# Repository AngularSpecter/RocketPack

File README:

*** Rocket Pack************************************

Project Synopsis
--------------------

Rocket pack is a development board based around the MSP430FR5739 microcontroller
and the Digi Xbee S3B Pro 900MHz zigbee radio.  The board is intended to 
facilitate broadcasting real time, high-rate sensor data over a range of several
hundred meters.  The board is designed to interface with custom built sensor 
packages, or with the TI sensorTag development board running custom firmware

Power Supply
----------------------
The board has on-board battery management designed specifically for single cell
lipo batteries, but will also take any voltage source between 3.3V and 5VDC.
The regualted 3.2V rail is availible on all three expansion headers as well as 
the CCdebugger header, which is designed specifically to power the sensorTag
development board.   

Communications
----------------------
The MSP430FR5739 contains two hardware USART's.  One USART is reserved for the
zigbee radio, while the other is broken out to both the serial data header and 
the ez430 programming/debug header.  All signals reqired for I2C, SPI or UART 
are availible on the serial data header

The firmware is written to buffer both inbound and outbound traffic.  The MCU 
pops bytes into the rx buffers in low power mode.  Once a line term char is RX'd,
LPM is exited and the full packet is processed.

No data is transmitted until a full packet is buffered.  Then it is transmitted
entirely before additional data is processed.  

Node power up sequence
-----------------------------------

sleep loop
-----------
1. Boot
2. Hold sensors in reset
3. Read and store radio address
4. Boot sensors
5. Read and store cal data
6. Sleep sensors

{
Auto discovery
---------------------
1. Poll magentometer
2. Broadcast host discover on trigger
3. Repeat until node select rxd
4. TX ACK
}

Wake up loop (on rx of node select)
-------------
7. TX ACK
8. Wait for command
   8a. Send cal data
   8b. Start data stream
  
On ~node select
----------------
1. Sleep sensors
2. Wait for wake up 

  Packet Formatting
  -----------------------------------------
  [0x01] [address] [0x00]
  host discover   0x01     Broadcast by the host to the base station to announce
                           its presence.
  [0x02] [command] [data] [0x00]                         
  command         0x02     Base -> node: command for remote node to execute
                           node -> base: return of command
                           
                  commands
                     0x01  Stop transmitting data
                     0x02  Start transmitting data
                     0x03  Change sensor profile
                     0x04  Reboot         

  cal data        0x03     Base -> node: Request calibration data 
                           node -> base: Return calibration data   
  
  data packet     0x04     node -> base: Data 

  node select     0x05     base -> node: address of node to be active..all other sleep

  ACK             0x06     command ACK
  
  NACK            0x07     command NACK
SensorTag
----------------------

 Errata
 ---------------------
 
 V0.1:
       Debug header location:  The location of the debug header interferes with 
       nearby pin headers, making it impossible to populate the debug header 
       with a right angle header and .1" pitch pin header.
       
       Specified load capacitors on the crystal are wrong.  The crystal will 
       stabilize on boot, but will not remain.
       
       Radio CONFIG pin is wired to MCU to allow easy entrance into command
       mode.  This should be connected to a different pin.

TO DO
------------------------

1.  MS430Firmware:  1.  Startup sleep mode -> poll mag and exit on high value
                    2.  Startup procedure -> broadcast calibration data
                    3.  Startup procedure -> read radio ID to store UID
                    4.  TX mirror         -> Prepend UID to TX'd packets
                    
2.  SensorTag       1.  Clean up firmware  -> remove deadwood
                    2.  
                    
3.  Labview         1.  Radio interface  ->  AT command mode control to select
                                             radio to listen to
                    2.  Sensor interface ->  Formalize calibration code
                    3.  Sensor interface ->  Formalize data processing
                    4.  Sensor interface ->  Add "remote globals"

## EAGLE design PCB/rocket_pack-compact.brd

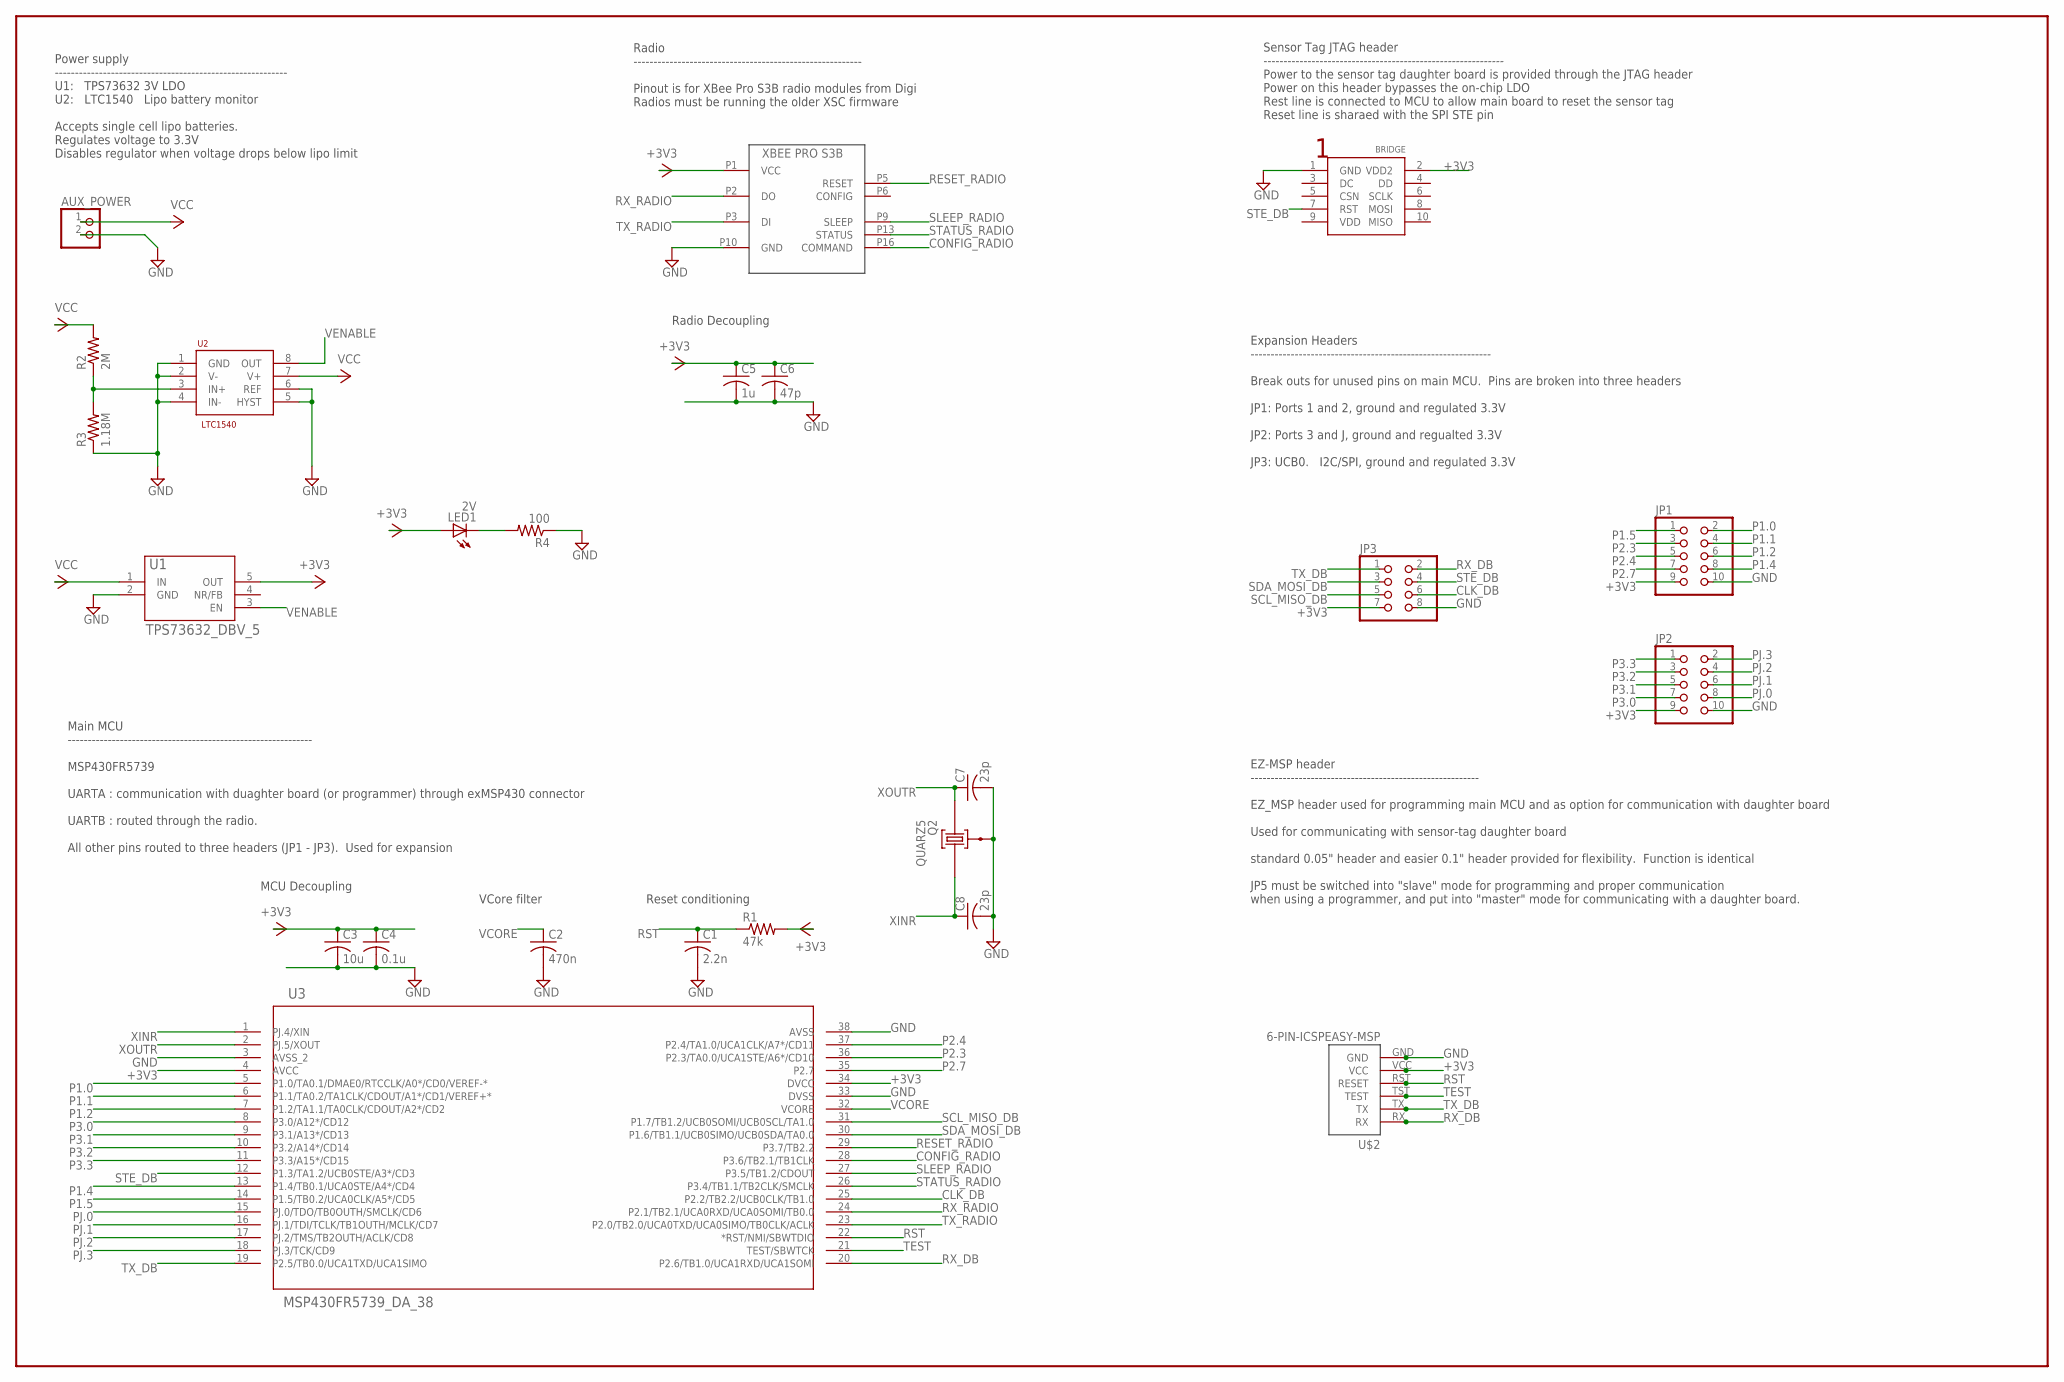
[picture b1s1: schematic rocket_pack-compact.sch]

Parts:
AUX_POWER: PINHD-1X2; 1X02
BRIDGE: CC-DEBUG; 2X5-1.27MM
C1: 2.2n; C1206
C2: 470n; C1206
C3: 10u; C1206
C4: 0.1u; C1206
C5: 1u; C1206
C6: 47p; C1206
C7, C8: 23p; C1206
JP1, JP2: PINHD-2X5; 2X05
JP3: PINHD-2X4; 2X04
LED1: 2V; 1206
Q2: QUARZ5
R1: 47k; R1206
R2: 2M; R1206
R3: 1.18M; R1206
R4: 100; R1206
U1: TPS73632_DBV_5; DBV5
U2: LTC1540; S8
U3: MSP430FR5739_DA_38; DA38
U$1: XBEE_PRO_S3B; PRO_S3B
U$2: 6-PIN-ICSPEASY-MSP; EASYMSP-6PIN

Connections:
+3V3: BRIDGE.2 (VDD2), C3.1, C4.1, C5.1, C6.1, JP1.9, JP2.9, JP3.7, LED1.A, R1.2, U1.5 (OUT), U3.4 (AVCC), U3.34 (DVCC), U$1.P1 (VCC), U$2.VCC
CLK_DB: JP3.6, U3.25 (P2.2/TB2.2/UCB0CLK/TB1.0)
CONFIG_RADIO: U3.28 (P3.6/TB2.1/TB1CLK), U$1.P16 (COMMAND)
GND: AUX_POWER.2, BRIDGE.1 (GND), C1.2, C2.2, C3.2, C4.2, C5.2, C6.2, C7.2, C8.2, JP1.10, JP2.10, JP3.8, Q2.GND@0 (0), R3.1, R4.1, U1.2 (GND), U2.1 (GND), U2.2 (V-), U2.4 (IN-), U2.5 (HYST), U2.6 (REF), U3.3 (AVSS_2), U3.33 (DVSS), U3.38 (AVSS), U$1.P10 (GND), U$2.GND
LED: LED1.C, R4.2
unnamed: R2.1, R3.2, U2.3 (IN+)
P1.0: JP1.2, U3.5 (P1.0/TA0.1/DMAE0/RTCCLK/A0*/CD0/VEREF-*)
P1.1: JP1.4, U3.6 (P1.1/TA0.2/TA1CLK/CDOUT/A1*/CD1/VEREF+*)
P1.2: JP1.6, U3.7 (P1.2/TA1.1/TA0CLK/CDOUT/A2*/CD2)
P1.4: JP1.8, U3.13 (P1.4/TB0.1/UCA0STE/A4*/CD4)
P1.5: JP1.1, U3.14 (P1.5/TB0.2/UCA0CLK/A5*/CD5)
P2.3: JP1.3, U3.36 (P2.3/TA0.0/UCA1STE/A6*/CD10)
P2.4: JP1.5, U3.37 (P2.4/TA1.0/UCA1CLK/A7*/CD11)
P2.7: JP1.7, U3.35 (P2.7)
P3.0: JP2.7, U3.8 (P3.0/A12*/CD12)
P3.1: JP2.5, U3.9 (P3.1/A13*/CD13)
P3.2: JP2.3, U3.10 (P3.2/A14*/CD14)
P3.3: JP2.1, U3.11 (P3.3/A15*/CD15)
PJ.0: JP2.8, U3.15 (PJ.0/TDO/TB0OUTH/SMCLK/CD6)
PJ.1: JP2.6, U3.16 (PJ.1/TDI/TCLK/TB1OUTH/MCLK/CD7)
PJ.2: JP2.4, U3.17 (PJ.2/TMS/TB2OUTH/ACLK/CD8)
PJ.3: JP2.2, U3.18 (PJ.3/TCK/CD9)
RESET_RADIO: U3.29 (P3.7/TB2.2), U$1.P5 (RESET)
RST: C1.1, R1.1, U3.22 (*RST/NMI/SBWTDIO), U$2.RST (RESET)
RX_DB: JP3.2, U3.20 (P2.6/TB1.0/UCA1RXD/UCA1SOMI), U$2.RX
RX_RADIO: U3.24 (P2.1/TB2.1/UCA0RXD/UCA0SOMI/TB0.0), U$1.P2 (DO)
SCL_MISO_DB: JP3.5, U3.31 (P1.7/TB1.2/UCB0SOMI/UCB0SCL/TA1.0)
SDA_MOSI_DB: JP3.3, U3.30 (P1.6/TB1.1/UCB0SIMO/UCB0SDA/TA0.0)
SLEEP_RADIO: U3.27 (P3.5/TB1.2/CDOUT), U$1.P9 (SLEEP)
STATUS_RADIO: U3.26 (P3.4/TB1.1/TB2CLK/SMCLK), U$1.P13 (STATUS)
STE_DB: BRIDGE.7 (RST), JP3.4, U3.12 (P1.3/TA1.2/UCB0STE/A3*/CD3)
TEST: U3.21 (TEST/SBWTCK), U$2.TST (TEST)
TX_DB: JP3.1, U3.19 (P2.5/TB0.0/UCA1TXD/UCA1SIMO), U$2.TX
TX_RADIO: U3.23 (P2.0/TB2.0/UCA0TXD/UCA0SIMO/TB0CLK/ACLK), U$1.P3 (DI)
VCC: AUX_POWER.1, R2.2, U1.1 (IN), U2.7 (V+)
VCORE: C2.1, U3.32 (VCORE)
VENABLE: U1.3 (EN), U2.8 (OUT)
XINR: C8.1, Q2.1, U3.1 (PJ.4/XIN)
XOUTR: C7.1, Q2.2, U3.2 (PJ.5/XOUT)

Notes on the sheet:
Radio Decoupling
MCU Decoupling
Power supply ---------------------------------------------------------- U1: TPS73632 3V LDO U2: LTC1540 Lipo battery monitor Accepts single cell lipo batteries. Regulates voltage to 3.3V Disables regulator when voltage drops below lipo limit
Radio --------------------------------------------------------- Pinout is for XBee Pro S3B radio modules from Digi Radios must be running the older XSC firmware
Sensor Tag JTAG header ------------------------------------------------------------ Power to the sensor tag daughter board is provided through the JTAG header Power on this header bypasses the on-chip LDO Rest line is connected to MCU to allow main board to reset the sensor tag Reset line is sharae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
Reset conditioning
VCore filter
Main MCU ------------------------------------------------------------- MSP430FR5739 UARTA : communication with duaghter board (or programmer) through exMSP430 connector UARTB : routed through the radio. All other pins routed to three headers (JP1 - JP3). Used for expansion
EZ-MSP header --------------------------------------------------------- EZ_MSP header used for programming main MCU and as option for communication with daughter board Used for communicating with sensor-tag daughter board standard 0.05" header and easier 0.1" header provided for flexibility. Functi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
Expansion Headers ------------------------------------------------------------ Break outs for unused pins on main MCU. Pins are broken into three headers JP1: Ports 1 and 2, ground and regulated 3.3V JP2: Ports 3 and J, ground and regualted 3.3V JP3: UCB0. I2C/SPI, ground and regulated 3.3V

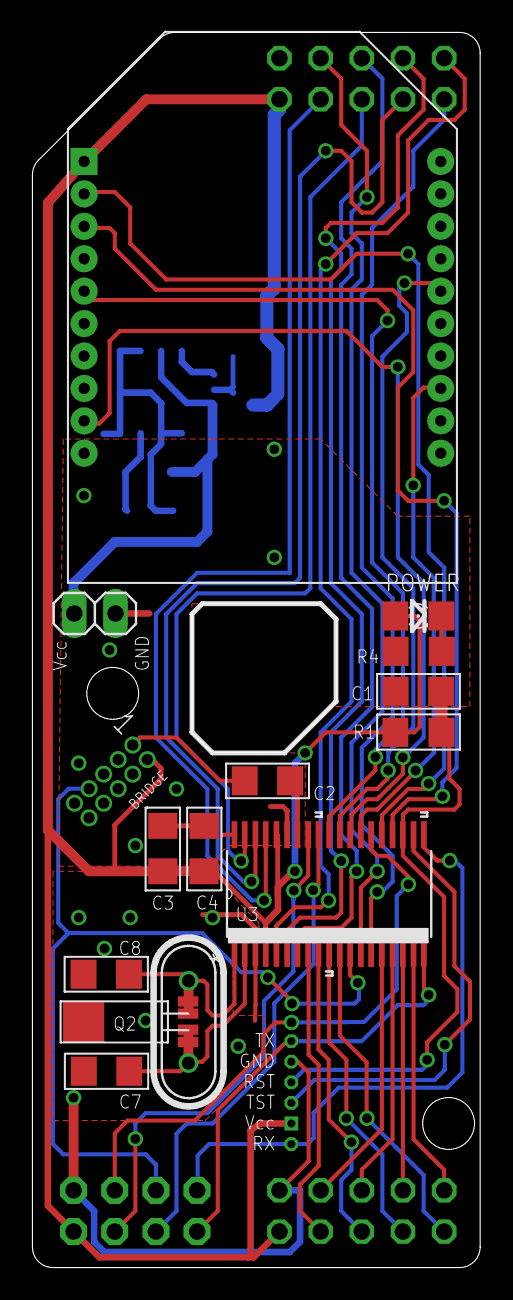
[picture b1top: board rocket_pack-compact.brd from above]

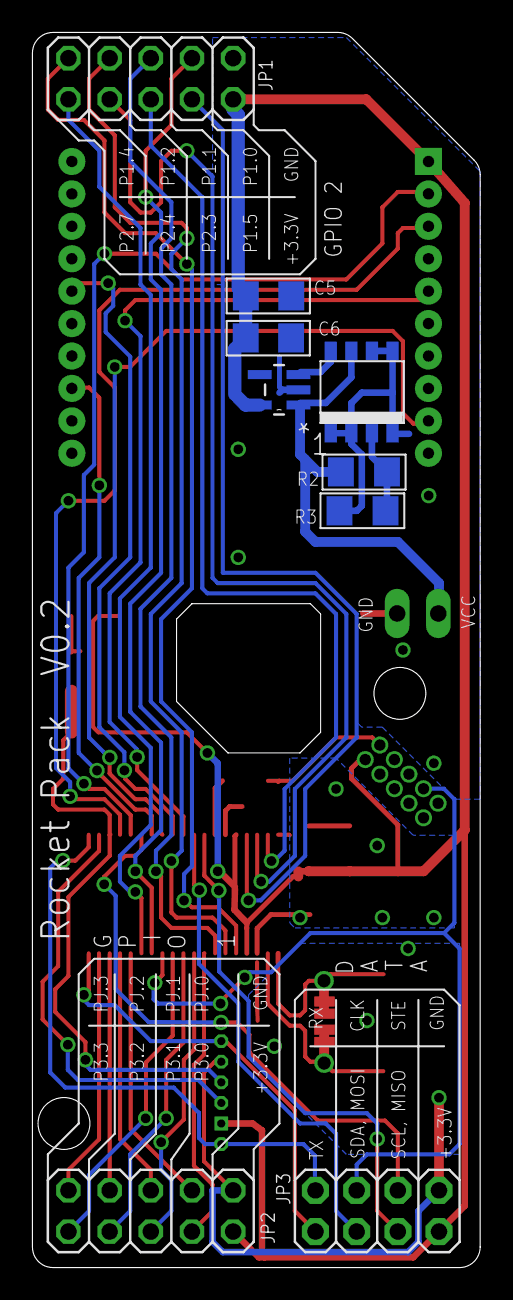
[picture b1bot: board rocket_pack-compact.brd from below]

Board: 2 copper layers, 27.6 x 76.2 mm, 24 parts (9 on the bottom side), 39 nets.

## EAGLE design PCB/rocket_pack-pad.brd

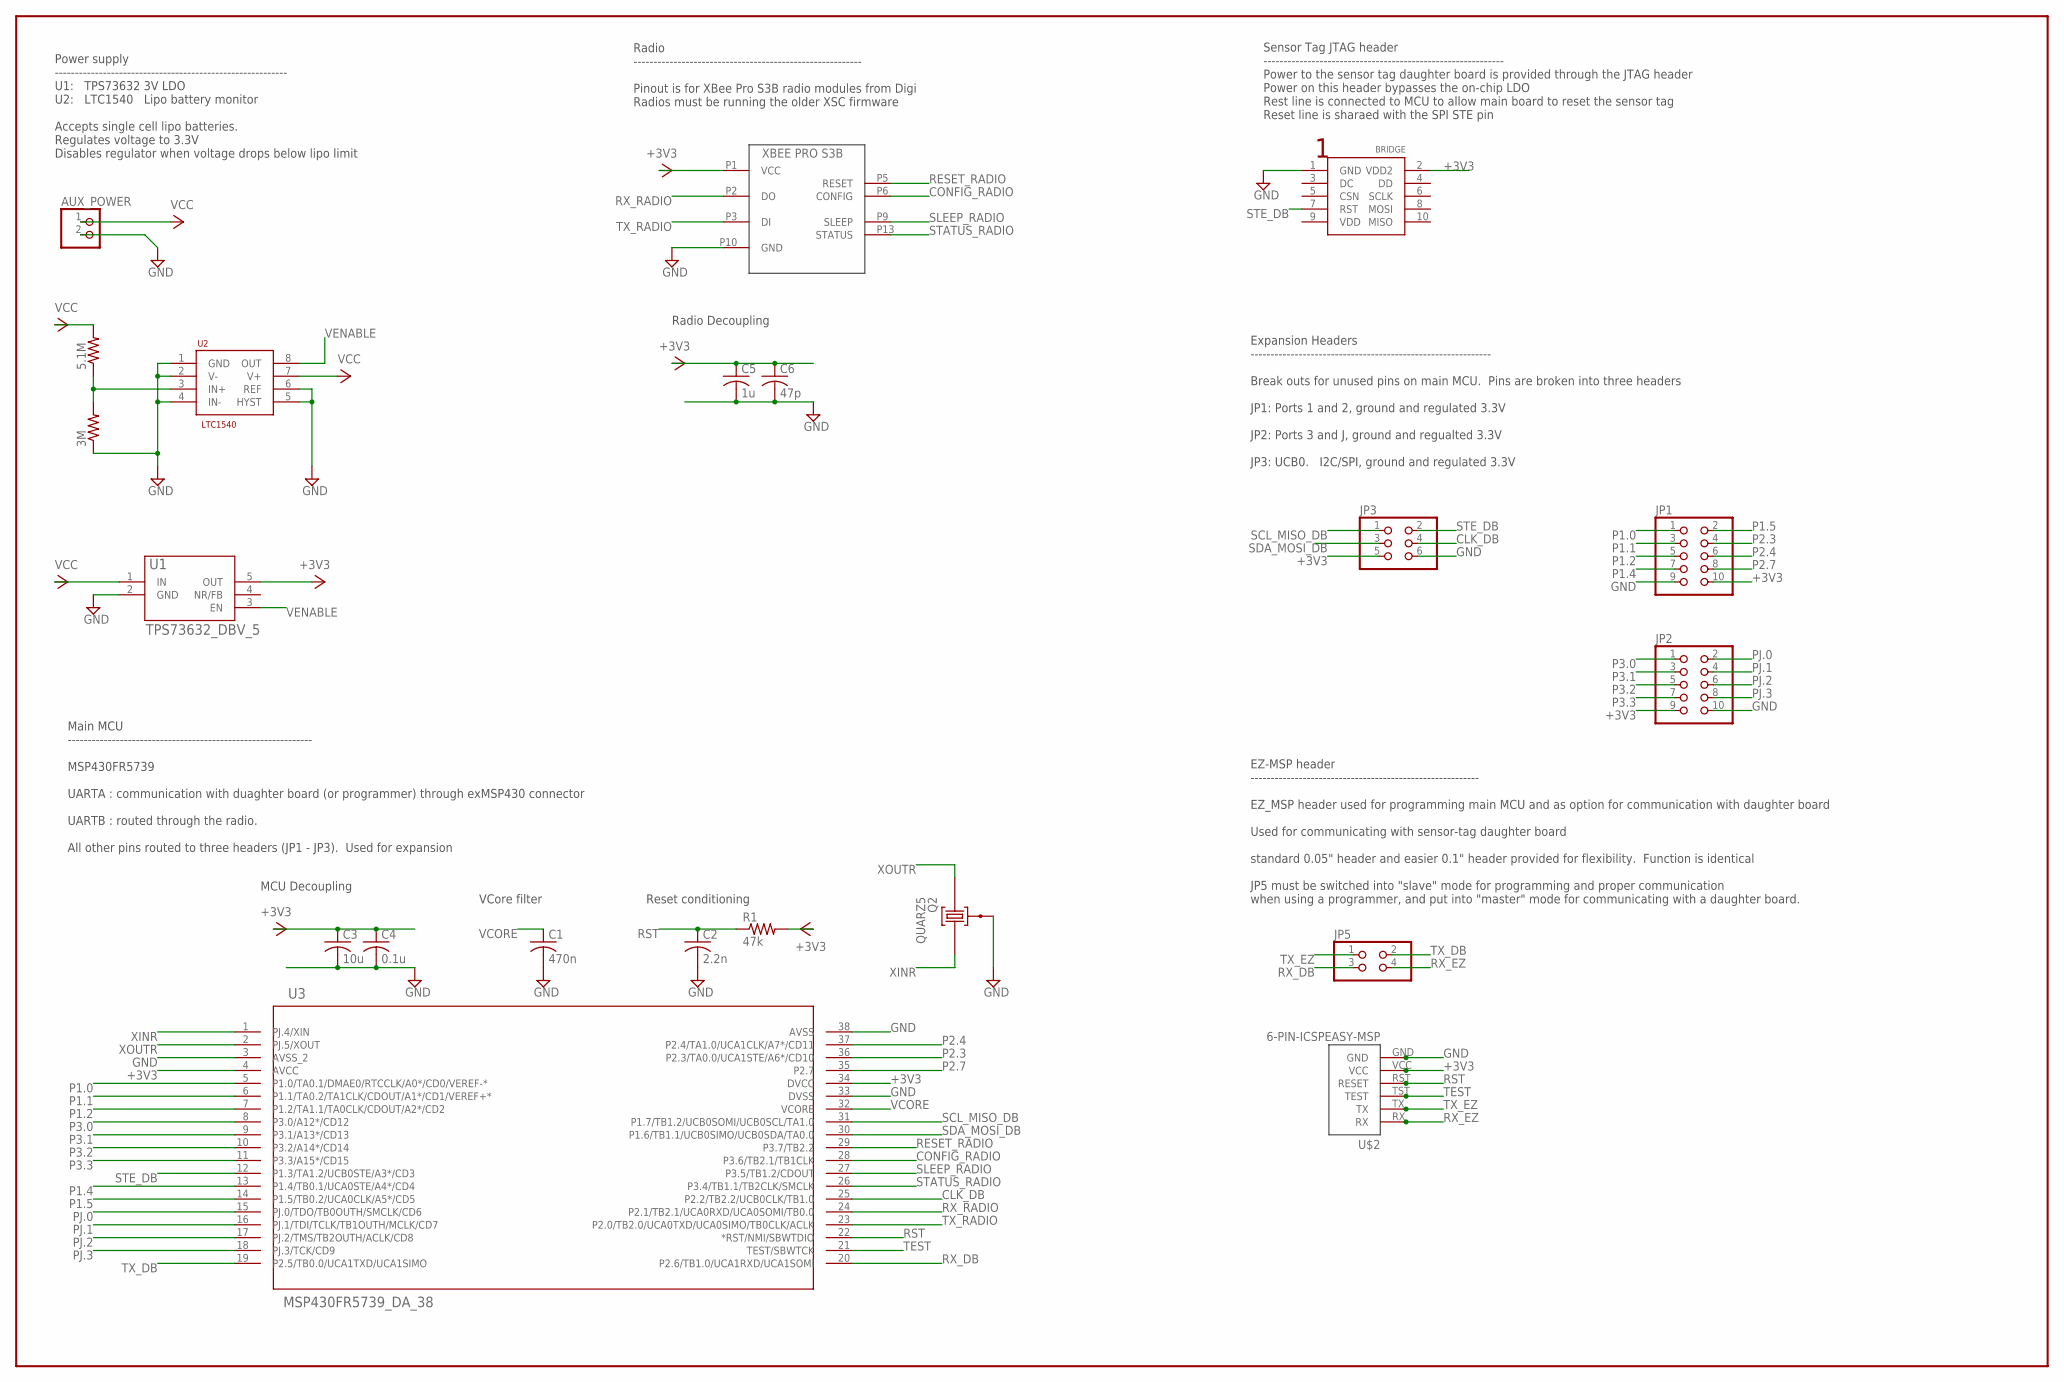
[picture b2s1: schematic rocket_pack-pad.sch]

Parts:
3M, 5.1M: R-US_R1206; R1206
AUX_POWER: PINHD-1X2; 1X02
BRIDGE: CC-DEBUG; 2X5-1.27MM
C1: 470n; C1206
C2: 2.2n; C1206
C3: 10u; C1206
C4: 0.1u; C1206
C5: 1u; C1206
C6: 47p; C1206
JP1, JP2: PINHD-2X5; 2X05
JP3: PINHD-2X3; 2X03
JP5: PINHD-2X2; 2X02
Q2: QUARZ5
R1: 47k; R1206
U1: TPS73632_DBV_5; DBV5
U2: LTC1540; S8
U3: MSP430FR5739_DA_38; DA38
U$1: XBEE_PRO_S3B; PRO_S3B
U$2: 6-PIN-ICSPEASY-MSP; EASYMSP-6PIN

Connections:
+3V3: BRIDGE.2 (VDD2), C3.1, C4.1, C5.1, C6.1, JP1.10, JP2.9, JP3.5, R1.2, U1.5 (OUT), U3.4 (AVCC), U3.34 (DVCC), U$1.P1 (VCC), U$2.VCC
CLK_DB: JP3.4, U3.25 (P2.2/TB2.2/UCB0CLK/TB1.0)
CONFIG_RADIO: U3.28 (P3.6/TB2.1/TB1CLK), U$1.P6 (CONFIG)
GND: 3M.1, AUX_POWER.2, BRIDGE.1 (GND), C1.2, C2.2, C3.2, C4.2, C5.2, C6.2, JP1.9, JP2.10, JP3.6, Q2.GND@0 (0), U1.2 (GND), U2.1 (GND), U2.2 (V-), U2.4 (IN-), U2.5 (HYST), U2.6 (REF), U3.3 (AVSS_2), U3.33 (DVSS), U3.38 (AVSS), U$1.P10 (GND), U$2.GND
unnamed: 3M.2, 5.1M.1, U2.3 (IN+)
P1.0: JP1.1, U3.5 (P1.0/TA0.1/DMAE0/RTCCLK/A0*/CD0/VEREF-*)
P1.1: JP1.3, U3.6 (P1.1/TA0.2/TA1CLK/CDOUT/A1*/CD1/VEREF+*)
P1.2: JP1.5, U3.7 (P1.2/TA1.1/TA0CLK/CDOUT/A2*/CD2)
P1.4: JP1.7, U3.13 (P1.4/TB0.1/UCA0STE/A4*/CD4)
P1.5: JP1.2, U3.14 (P1.5/TB0.2/UCA0CLK/A5*/CD5)
P2.3: JP1.4, U3.36 (P2.3/TA0.0/UCA1STE/A6*/CD10)
P2.4: JP1.6, U3.37 (P2.4/TA1.0/UCA1CLK/A7*/CD11)
P2.7: JP1.8, U3.35 (P2.7)
P3.0: JP2.1, U3.8 (P3.0/A12*/CD12)
P3.1: JP2.3, U3.9 (P3.1/A13*/CD13)
P3.2: JP2.5, U3.10 (P3.2/A14*/CD14)
P3.3: JP2.7, U3.11 (P3.3/A15*/CD15)
PJ.0: JP2.2, U3.15 (PJ.0/TDO/TB0OUTH/SMCLK/CD6)
PJ.1: JP2.4, U3.16 (PJ.1/TDI/TCLK/TB1OUTH/MCLK/CD7)
PJ.2: JP2.6, U3.17 (PJ.2/TMS/TB2OUTH/ACLK/CD8)
PJ.3: JP2.8, U3.18 (PJ.3/TCK/CD9)
RESET_RADIO: U3.29 (P3.7/TB2.2), U$1.P5 (RESET)
RST: C2.1, R1.1, U3.22 (*RST/NMI/SBWTDIO), U$2.RST (RESET)
RX_DB: JP5.3, U3.20 (P2.6/TB1.0/UCA1RXD/UCA1SOMI)
RX_EZ: JP5.4, U$2.RX
RX_RADIO: U3.24 (P2.1/TB2.1/UCA0RXD/UCA0SOMI/TB0.0), U$1.P2 (DO)
SCL_MISO_DB: JP3.1, U3.31 (P1.7/TB1.2/UCB0SOMI/UCB0SCL/TA1.0)
SDA_MOSI_DB: JP3.3, U3.30 (P1.6/TB1.1/UCB0SIMO/UCB0SDA/TA0.0)
SLEEP_RADIO: U3.27 (P3.5/TB1.2/CDOUT), U$1.P9 (SLEEP)
STATUS_RADIO: U3.26 (P3.4/TB1.1/TB2CLK/SMCLK), U$1.P13 (STATUS)
STE_DB: BRIDGE.7 (RST), JP3.2, U3.12 (P1.3/TA1.2/UCB0STE/A3*/CD3)
TEST: U3.21 (TEST/SBWTCK), U$2.TST (TEST)
TX_DB: JP5.2, U3.19 (P2.5/TB0.0/UCA1TXD/UCA1SIMO)
TX_EZ: JP5.1, U$2.TX
TX_RADIO: U3.23 (P2.0/TB2.0/UCA0TXD/UCA0SIMO/TB0CLK/ACLK), U$1.P3 (DI)
VCC: 5.1M.2, AUX_POWER.1, U1.1 (IN), U2.7 (V+)
VCORE: C1.1, U3.32 (VCORE)
VENABLE: U1.3 (EN), U2.8 (OUT)
XINR: Q2.1, U3.1 (PJ.4/XIN)
XOUTR: Q2.2, U3.2 (PJ.5/XOUT)

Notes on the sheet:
Radio Decoupling
MCU Decoupling
Power supply ---------------------------------------------------------- U1: TPS73632 3V LDO U2: LTC1540 Lipo battery monitor Accepts single cell lipo batteries. Regulates voltage to 3.3V Disables regulator when voltage drops below lipo limit
Radio --------------------------------------------------------- Pinout is for XBee Pro S3B radio modules from Digi Radios must be running the older XSC firmware
Sensor Tag JTAG header ------------------------------------------------------------ Power to the sensor tag daughter board is provided through the JTAG header Power on this header bypasses the on-chip LDO Rest line is connected to MCU to allow main board to reset the sensor tag Reset line is sharae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
Reset conditioning
VCore filter
Main MCU ------------------------------------------------------------- MSP430FR5739 UARTA : communication with duaghter board (or programmer) through exMSP430 connector UARTB : routed through the radio. All other pins routed to three headers (JP1 - JP3). Used for expansion
EZ-MSP header --------------------------------------------------------- EZ_MSP header used for programming main MCU and as option for communication with daughter board Used for communicating with sensor-tag daughter board standard 0.05" header and easier 0.1" header provided for flexibility. Functi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
Expansion Headers ------------------------------------------------------------ Break outs for unused pins on main MCU. Pins are broken into three headers JP1: Ports 1 and 2, ground and regulated 3.3V JP2: Ports 3 and J, ground and regualted 3.3V JP3: UCB0. I2C/SPI, ground and regulated 3.3V

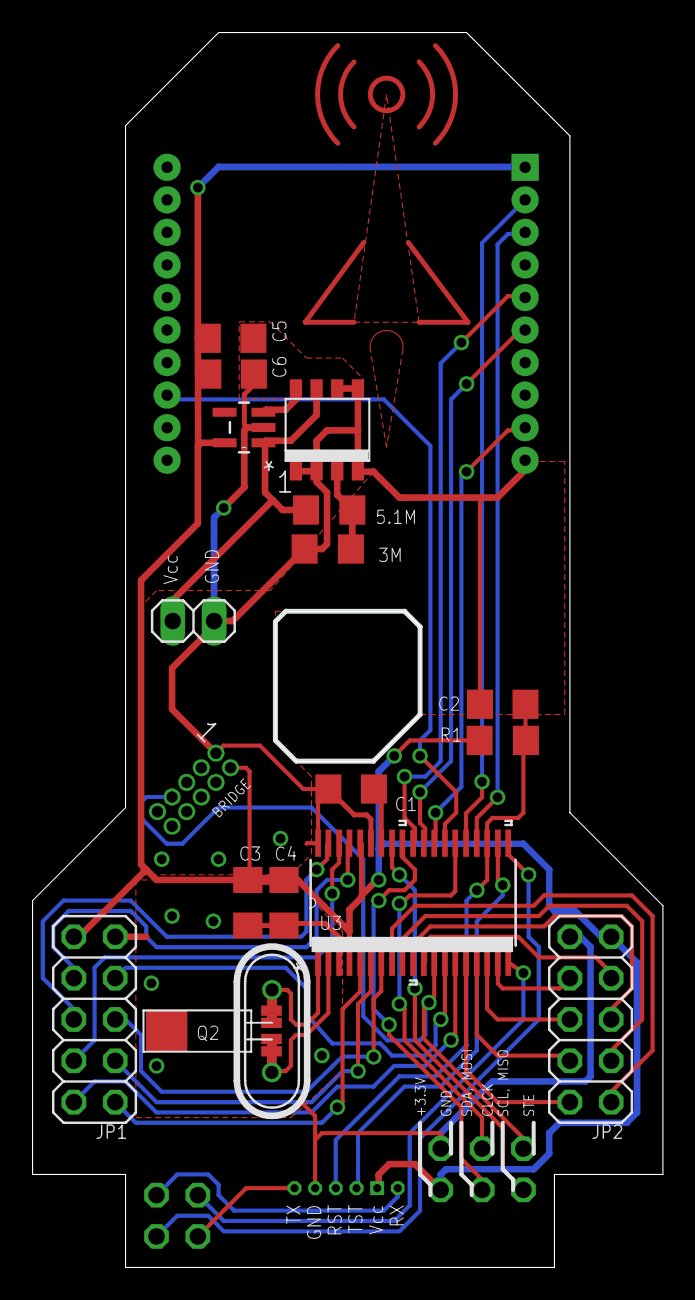
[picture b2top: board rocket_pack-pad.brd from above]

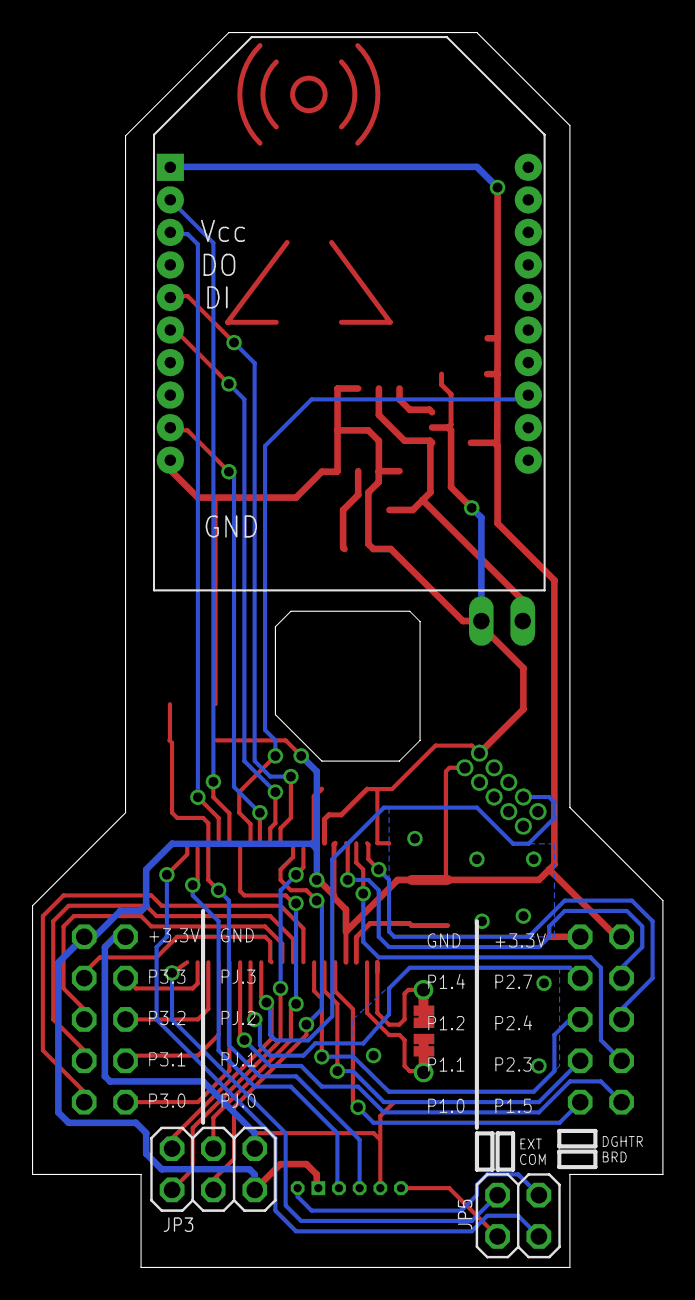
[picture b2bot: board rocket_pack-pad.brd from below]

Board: 2 copper layers, 38.7 x 75.9 mm, 21 parts (3 on the bottom side), 40 nets.

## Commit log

2014-01-17 Initial Commit
    Checking in V0.1 PCB's.
2014-01-17 Sensor tag firmware
    Added sensor tag firmware
    Added supporting HAL files from TI BTLE stack
    Added IAR build environment
2014-01-25 Adding base code for MSP430
2014-01-25 Revert "Sensor tag firmware"
    This reverts commit df802b2d434db3963c2185d4e9ccf82e98226f94.
2014-01-27 attempted to add in lower power...no more room
2014-01-31 sleep timer and 'zero' header
2014-02-03 auto and manual polling modes
2014-02-04 Started rocket pack firmware
    Initial start to firmware for MSP430FR5739 board
    UART and clock initialization code
2014-02-05 firmware + PCB update
    Start of main firmware..mainly UART code
    Update to PCB to move "command" line from radio pin 6 to 16. Pin 6
    enters command mode on boot, pin 16 enables binary command mode
    (allowing the serial +++ handshake to be bypassed
2014-02-06 Firmware updates
    Added delay timing functionality
    Started hashing out radio command/control
2014-02-16 sensor updates
    Fixed issue with magnetometer and gyro in tag firmware
    Updated labview code to match
    Decreased poll rate of barometer to half the main update rate. Can hit
    ~20Hz with everything but humidity (with temp/pressure at 10Hz) and 15Hz
    with everything (temp/press at 7 Hz).
2014-02-16 Added README
2014-02-17 Added License
2014-02-18 Fixing artifacts from merge
2014-03-24 Added sensor state machine
    Sensor state machine added with startup/shutdown handshaking sequence
    with base station as well as heartbeat.
    Issue with incoming (from base station) commands being blocked when
    radio is burst transmitting data.
2014-04-04 labview + MSP firmware
    Moved sensor polling to the MSP430 firmware (timer triggered) to
    generate uniform data rate
    addressed some bugs
    Working, single channel labview interface code
2014-04-13 better startup behavior in labView code
2014-04-14 Version 0.2
    Moved programming header to no longer interfere with headers
    Fixed pinout on radio module to allow binary programming
    Added power indicator LED
